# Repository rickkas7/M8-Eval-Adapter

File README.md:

# M8-Eval-Adapter

**Hardware design to facilitate prototyping Tracker One designs on the Tracker SoM Evaluation Board**

This is a simple board you can assemble that makes it easier to prototype designs that will eventually use the Tracker One or Tracker SoM Carrier Board, using the Tracker SoM Evaluation Board.

It fits on the 40 pin expansion connector on the Tracker SoM Evaluation Board and includes features that are on the Tracker One and Tracker Carrier Board:

- B8B-PH connector on the board, the same connector as on the Tracker Carrier Board
- Thermistor (temperature sensor) connected to A0.
- USER button connected to A1
- Blue GNSS LED connected to A2
- CAN connection

The CAN connection is necessary because CAN is not exposed on the 40-pin header. Short wires connect to the screw terminals on the Tracker SoM evaluation board so the CAN will be available on the M8 connector.

**Note:** The Tracker One supports up to 30V on the M8 connector. This adapter board does not have the same power supply as the Tracker One and Tracker Carrier Board. **This adapter board only supports up to 12V using the B8B-PH as a power input!** 

## About the M8 and B8B-PH Connector

The Tracker Carrier Board in the Tracker One has a B8B-PH connector on the board.

The Tracker One has a small cable with a PHR-8 connector (fits into the B8B-PH) on one end and an M8 8-pin male IP67 on the other. The M8 end fits into a hole in the case. This is the cable inside the Tracker One:

Your Tracker One project will typically use a M8 8-pin female cable. Here's one that has wires on the other end.

You'd typically connect those wires to your custom expansion board using one of several methods:

- Terminate with pins in a PHR-8 to mate with a B8B-PH on your expansion board
- Terminate with screw terminals on your board
- Terminate by soldering the wires to your board

For prototyping, you can just skip the M8 cable and use PHR-8 to wires, or a PHR-8 to PHR-8 cable, as in this example:

## Design

### Schematic

### Board

The Eagle CAD files (.sch and .brd) are in the [Github repository](https://github.com/rickkas7/M8-Eval-Adapter), along with the Gerber files.

## BoM (Bill of Materials)

| Quan | Part | Example | Price | 
| :---: | --- | --- | ---: |
| 1 | 100K NTC Thermistor | [Panasonic ERT-J1VR104FM](https://www.digikey.com/product-detail/en/panasonic-electronic-components/ERT-J1VR104FM/P122067CT-ND/7069667) | $0.39 |
| 2 | 100 ohm resistor 0603 | [Panasonic ERJ-3GEYJ101V](https://www.digikey.com/product-detail/en/panasonic-electronic-components/ERJ-3GEYJ101V/P100GCT-ND/134714) | | 
| 1 | 100K resistor 0603 | [Panasonic ERJ-3EKF1003V](https://www.digikey.com/product-detail/en/panasonic-electronic-components/ERJ-3EKF1003V/P100KHCT-ND/198110) | | 
| 1 | Blue LED 0603 | [Lite-On LTST-C193TBKT-5A](https://www.digikey.com/product-detail/en/lite-on-inc/LTST-C193TBKT-5A/160-1827-1-ND/2355044) | $0.47 |
| 1 | 4.5mm momentary switch | [E Switch TL3305AF160QG](https://www.digikey.com/product-detail/en/e-switch/TL3305AF160QG/EG5350CT-ND/5816195) | $0.20 |
| 1 | B8B-PH Connector | [JST B8B-PH-SM4-TB(LF)(SN)](https://www.digikey.com/product-detail/en/jst-sales-america-inc/B8B-PH-SM4-TB-LF-SN/455-1740-1-ND/926837) | $1.00 |
| | Male header pins 0.1" | [Sullins PRPC040SAAN-RC](https://www.digikey.com/product-detail/en/PRPC040SAAN-RC/S1011EC-40-ND/2775214) | | 

## Assembly Diagram

## Enabling Firmware Features

To enable these features in the Tracker Edge firmware, edit tracker_config.h and make sure these are defined. They default to not being defined on the Tracker SoM Evaluation board.

```
#define TRACKER_THERMISTOR                    (A0)
#define TRACKER_USER_BUTTON                   (A1)
#define TRACKER_GNSS_LOCK_LED                 (A2)
```

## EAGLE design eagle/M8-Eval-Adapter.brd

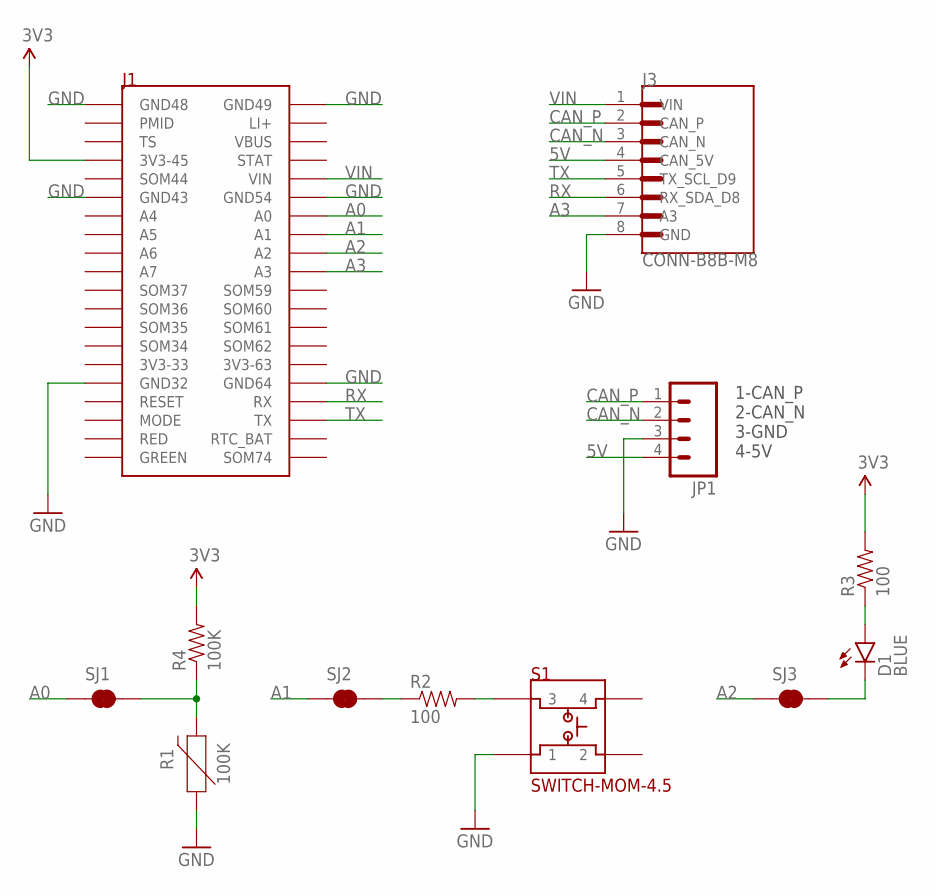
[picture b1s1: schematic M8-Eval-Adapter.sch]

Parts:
D1: BLUE; LED-0603
J1: HDR-TRACKER-EVAL-MAIN
J3: CONN-B8B-M8; JST_B8B-PH-SM4-TB(LF)(SN)
JP1: M04PTH; 1X04
R1: 100K; 0603
R2, R3: 100; 0603-RES
R4: 100K; 0603-RES
S1: SWITCH-MOM-4.5
SJ1, SJ2, SJ3: JUMPER-PAD-2-NC_BY_TRACENO_SILK; PAD-JUMPER-2-NC_BY_TRACE_NO_SILK

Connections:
3V3: J1.3V3-45, R3.2, R4.2
5V: J3.4 (CAN_5V), JP1.4
A0: J1.A0, SJ1.1
A1: J1.A1, SJ2.1
A2: J1.A2, SJ3.1
A3: J1.A3, J3.7 (A3)
CAN_N: J3.3 (CAN_N), JP1.2
CAN_P: J3.2 (CAN_P), JP1.1
GND: J1.GND32, J1.GND43, J1.GND48, J1.GND49, J1.GND54, J1.GND64, J3.8 (GND), JP1.3, R1.1, S1.1
unnamed: R2.1, SJ2.2
unnamed: R1.2, R4.1, SJ1.2
unnamed: R2.2, S1.3
unnamed: D1.C, SJ3.2
unnamed: D1.A, R3.1
RX: J1.RX, J3.6 (RX_SDA_D8)
TX: J1.TX, J3.5 (TX_SCL_D9)
VIN: J1.VIN, J3.1 (VIN)

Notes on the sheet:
1-CAN_P 2-CAN_N 3-GND 4-5V

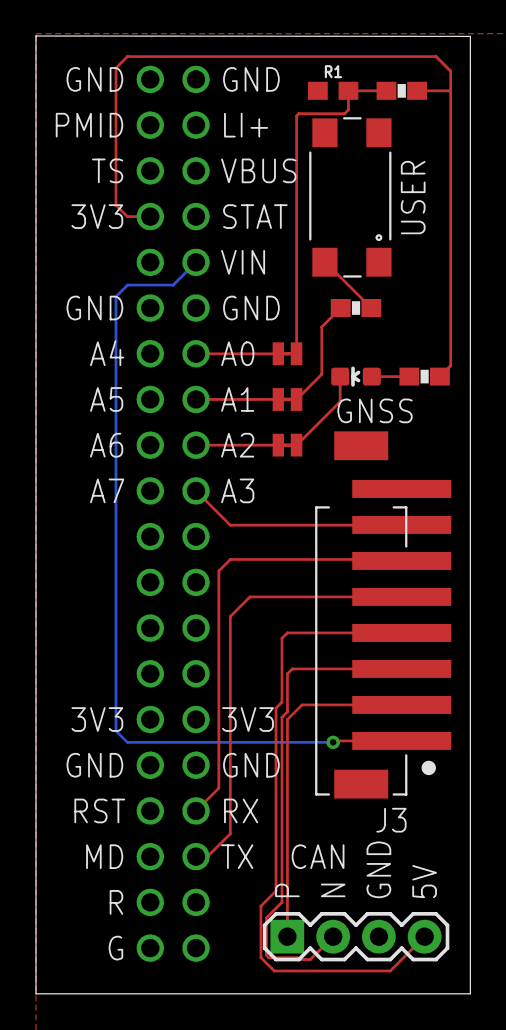
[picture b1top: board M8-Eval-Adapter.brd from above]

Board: 2 copper layers, 24.1 x 53.2 mm, 12 parts (0 on the bottom side), 17 nets.

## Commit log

2020-06-26 Initial checkin
2020-06-26 Add power supply note
2020-06-29 Fix typo
2020-06-29 Add firmware instructions
